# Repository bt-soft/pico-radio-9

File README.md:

# pico-radio-9

**A projekt még fejlesztés alatt áll!**

A projekt leírása: https://electrodiy.blog.hu/2026/01/01/pico_radio_fm_am_ssb_cw_rtty_sstv_wefax

## A kütyü

<br/>

<em>A kísérleti kütyü (egy V7-es prototípus hangfrekis műveleti erősítővel kiegészítve)</em>

<br/>

### PCB 3D View

<table style="border:none; width:100%;">
  <tr>
    <td style="border:none; text-align:center; vertical-align:middle;">
      
    </td>
    <td style="border:none; text-align:center; vertical-align:middle;">
      
    </td>
  </tr>
  <tr>
    <td style="border:none; text-align:center;">
      <em>Kétoldalas NYÁK terv</em>
    </td>
    <td style="border:none; text-align:center;">
      <em>Egyoldalas NYÁK terv</em>
    </td>
  </tr>
</table>

Egy Raspberry Pi Pico alapú rádióprojekt (Si4735 vezérléssel) — fejlett dekóderekkel (RTTY, CW, SSTV, WeFax), spektrum megjelenítéssel és interaktív érintőképernyős felülettel.

**Fő funkciók**
- Si4735 vezérlés (AM/FM/SDR jellegű demodok és RDS)
- Dekóderek: RTTY, CW, SSTV, WeFax, RTTY feldolgozó
- Valós idejű spektrum- és vízesés (low/high resolution bar, oscilloscope, envelope, waterfall, valamint CW/RTTY hangolássegéd waterfall és SNR burkoló) megjelenítők
- Hangfeldolgozó pipeline (AGC, FFT alapú vizualizáció manuális vagy automatikus erősítéssel)
- Rétegzett dialógus rendszer: többgombos dialógusok, értékmódosítók (rotary/touch)
- Konfigurációs tárolás EEPROM-ban (station/setting store)

## Architektúra
 - RP2040 / multicore: A Raspberry Pi Pico kétmagos RP2040 mikrovezérlője lehetővé teszi a feladatok elkülönítését (audio-feldolgozás a második magon, míg az első mag a UI/Si4735 vezérlést végzi). Ezt a projekt kihasználja a valós idejű audio dekódolás és UI műveletek párhuzamosítása érdekében.

## Technológiák

- Platform: Raspberry Pi Pico (RP2040)
- Fejlesztési környezet: PlatformIO 
- Framework: Arduino (RP2040 / Arduino core) 
- Nyelv: C++17 
- TFT vezérlés: `TFT_eSPI` — ILI9844 3.5" TFT grafikus megjelenítés és touch kezelése.
- Si4735 vezérlés: `PU2CLR SI4735` wrapper és a projekt saját `Si4735*` moduljai (I2C/SPI integráció és rádiófunkciók).
- Audio feldolgozás: FFT alapú spektrum- és vízesés (waterfall) megjelenítés, AGC és egyedi AudioProcessor pipeline.
- Dekóderek: RTTY, CW, SSTV, WeFax implementációk (saját `Decoder*` modulok).
- UI komponensek: egyedi komponenskeretrendszer (`UI*` osztályok) — dialógusok, többgombos menük, virtuális billentyűzet és grafikus komponensek.
- Időzítés és megszakítások: `RPI_PICO_TimerInterrupt` (PlatformIO lib) a pontos időzítéshez.
- FFT könyvtár: `arduinoFFT` a spektrum-számításokhoz.
- Helyi segédkönyvtárak: `lib/pico_sstv` az SSTV dekódoláshoz és segédfüggvényekhez.

## Felhasznált könyvtárak
- `Arduino-Pico`: https://github.com/earlephilhower/arduino-pico
- `TFT eSPI`: https://github.com/Bodmer/TFT_eSPI
- `RPI PICO TimerInterrupt`: https://github.com/khoih-prog/RPI_PICO_TimerInterrupt
- `PU2CLR SI4735`: https://github.com/pu2clr/SI4735
- `Arduino CMSIS-DSP`: https://www.arduinolibraries.info/libraries/arduino_cmsis-dsp
- `lib/pico_sstv`: https://github.com/dawsonjon/PicoSSTV

## Fájlok és modulok (összefoglaló)
- `src/` - forráskód (képernyők, dekóderek, UI komponensek, vezérlők)
  - `main.cpp`, `main-c1.cpp` - indító fájlok
  - `Screen*` - különböző képernyők (RTTY, CW, FM, AM, SSTV, WeFax, Setup, stb.)
  - `Decoder*` - dekóderek (RTTY, CW, SSTV, WeFax, stb.)
  - `UI*` - UI keretrensdszer komponensei (gombok, dialógusok, spektrum, textbox, stb.)
  - `Si4735*` - Si4735 kezelő és runtime logika
  - `AudioController.*`, `AudioProcessor-*` - audio pipeline és feldolgozás
- `include/` - header fájlok (összes osztály, UI, konfigurációs struktúrák)
  - `Config.h`, `ConfigData.h` - konfigurációs struktúrák és default értékek
  - `UIDialogBase.h`, `UIMultiButtonDialog.h`, `UIValueChangeDialog.h` - dialógusok és vezérlők
  - `UIHorizontalButtonBar.h` - alsó gombsor kezelése
- `lib/` - külső vagy saját könyvtárak (pl. `pico_sstv`, `CMSIS-DSP`)
- `doc/` - dokumentációs anyagok 
- `test/` - teszt erőforrások és példa adatállományok (pl. cw, rtty tesztek)

## Konfiguráció és mentés
- Konfigurációk a `Config` struktúrában találhatók (`include/Config.h`, `include/ConfigData.h`).
- Station / memory store beállítások EEPROM-ban tárolódnak (lásd `StationStore*` és `Eeprom*` fájlok).

## UI képernyők, dialógusok
- Rétegzett dialógus rendszer: a `UIScreen` tartalmaz egy dialógusstack-et, a `showDialog()` és `onDialogClosed()` mechanizmusokkal.
- Többgombos dialógusok: `UIMultiButtonDialog` + `UIValueChangeDialog` az értékek szerkesztéséhez.

## Szoftverarchitektúra
- Dekóderek: `src/Decoder*.cpp` — új dekóderek hozzáadása egyszerű az `IDecoder` interfész implementálásával.
- UI komponensek: `include/UI*`, `src/UI*` — gombok, dialógusok, új vizualizációk hozzáadása.
- Audio pipeline: `AudioController.cpp` és `AudioProcessor-*.cpp` fájlok tartalmazzák a feldolgozás logikáját.

## Hibakeresés / debug
- A forrásban `DEBUG(...)` makrók és logolási segédek találhatók. A debug build beállítása és a `__DEBUG` makró használata segíthet a problémakeresésben.

## Kapcsolási rajz / nyomtatott áramkör
- Kicad formátumban a `kicad` mappában (egy- és kétoldalas NYÁK tervvel).

---

## Harmadik féltől származó források
Az alábbi forrás nyújtottak inspirációkat a projekt fejlesztése és megvalósítása során.

 - **SI4735 + TFT példa (IU4ALH)**: https://github.com/IU4ALH/IU4ALH
  - Használat: Elsősorban a repó  `SI4735_2.8_TFT_SI5351_V.5.2b_Dark.zip` állományában található forrásokat használtam fel, amelyek inspirációt adtak a szolgáltatások, a képernyők felépítéséhez valamint az Si4735 beállítások kezeléséhez.

- **Rotary encoder / forgókapcsoló referencia**: https://www.mikrocontroller.net/articles/Drehgeber
  - Használat: A forgató encoder kezelésének elméleti háttere és debouncing/step logika inspirálására; segített a `RotaryEncoder` osztály és a forgóvezérlők finomhangolásában.

- **Pico SSTV implementáció**: https://github.com/dawsonjon/PicoSSTV
  - Használat: SSTV dekóder és mintafeldolgozó technikák inspirációjára használtam a projekt `DecoderSSTV` moduljának kialakításához.

- **fldigi**: https://github.com/w1hkj/fldigi
  - Használat: HF WeFax dekóder kiakalítása, technikai megoldások, szoftveres szűrők
---

## License
Projekt licenc: MIT

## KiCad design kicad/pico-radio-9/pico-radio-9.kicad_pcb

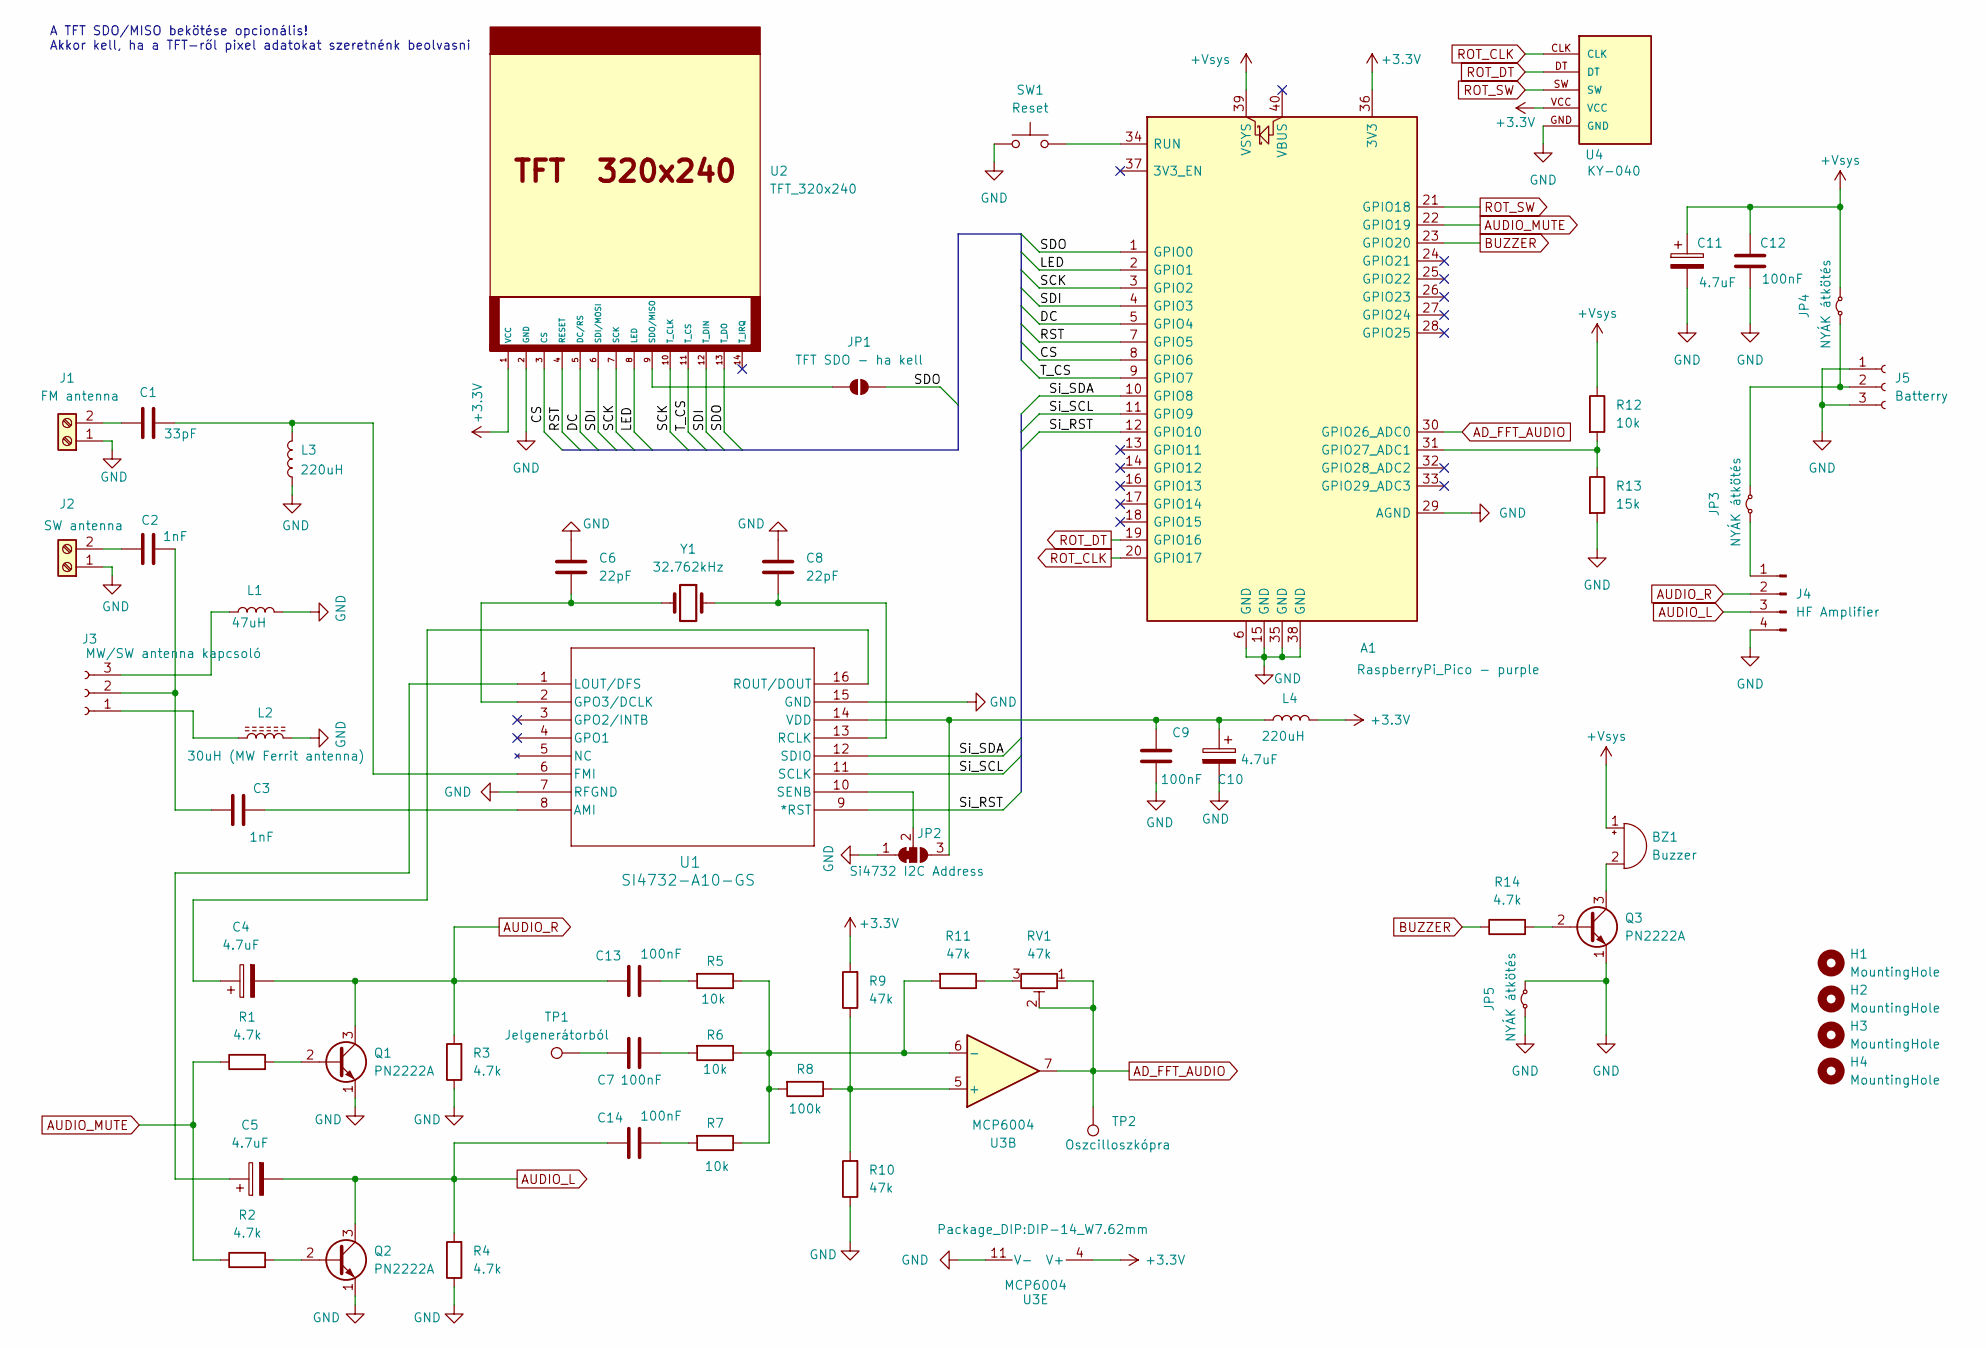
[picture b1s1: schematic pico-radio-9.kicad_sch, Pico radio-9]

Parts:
A1: RaspberryPi_Pico - purple; RaspberryPi_Pico_Common_THT-simple
BZ1: Buzzer; Buzzer_12x9.5RM7.6
C1: 33pF; C_Disc_D3.0mm_W1.6mm_P2.50mm
C2, C3: 1nF; C_Disc_D3.0mm_W1.6mm_P2.50mm
C4, C5, C10, C11: 4.7uF; CP_Radial_D5.0mm_P2.50mm
C6, C8: 22pF; C_Disc_D3.0mm_W1.6mm_P2.50mm
C7, C9, C12, C13, C14: 100nF; C_Disc_D7.0mm_W2.5mm_P5.00mm
H1, H2, H3, H4: MountingHole; MountingHole_3.2mm_M3
J1: FM antenna; TerminalBlock_4Ucon_1x02_P3.50mm_Horizontal
J2: SW antenna; TerminalBlock_4Ucon_1x02_P3.50mm_Horizontal
J3: MW/SW antenna kapcsoló; PinHeader_1x03_P2.54mm_Vertical
J4: HF Amplifier; PinHeader_1x04_P2.54mm_Vertical
J5: Batterry; PinHeader_1x03_P2.54mm_Vertical
JP1: TFT SDO - ha kell; SolderJumper-2_P1.3mm_Open_RoundedPad1.0x1.5mm
JP2: Si4732 I2C Address; SolderJumper-3_P1.3mm_Bridged12_RoundedPad1.0x1.5mm
JP3, JP4, JP5: NYÁK átkötés; R_Axial_DIN0207_L6.3mm_D2.5mm_P10.16mm_Horizontal
L1: 47uH; R_Axial_DIN0207_L6.3mm_D2.5mm_P10.16mm_Horizontal
L2: 30uH (MW Ferrit antenna); PinHeader_1x02_P2.54mm_Vertical
L3, L4: 220uH; R_Axial_DIN0207_L6.3mm_D2.5mm_P10.16mm_Horizontal
Q1, Q2, Q3: PN2222A; TO-92_Inline_Wide
R1, R2, R3, R4, R14: 4.7k; R_Axial_DIN0207_L6.3mm_D2.5mm_P10.16mm_Horizontal
R5, R6, R7, R12: 10k; R_Axial_DIN0207_L6.3mm_D2.5mm_P10.16mm_Horizontal
R8: 100k; R_Axial_DIN0207_L6.3mm_D2.5mm_P10.16mm_Horizontal
R9, R10, R11: 47k; R_Axial_DIN0207_L6.3mm_D2.5mm_P10.16mm_Horizontal
R13: 15k; R_Axial_DIN0207_L6.3mm_D2.5mm_P10.16mm_Horizontal
RV1: 47k; Potentiometer_Runtron_RM-063_Horizontal
SW1: Reset; PinHeader_1x02_P2.54mm_Vertical
TP1: Jelgenerátorból; TestPoint_Loop_D2.50mm_Drill1.0mm
TP2: Oszcilloszkópra; TestPoint_Loop_D2.50mm_Drill1.0mm
U1: SI4732-A10-GS; SOIC_A10-GS_SIL
U2: TFT_320x240; PinHeader_1x14_P2.54mm_Vertical
U3: MCP6004; DIP-14_W7.62mm
U4: KY-040; KY-040-PORT
Y1: 32.762kHz; Crystal_C38-LF_D3.0mm_L8.0mm_Horizontal

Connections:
+3.3V: A1.36 (3V3), L4.2, R9.2, U2.1 (VCC), U3.4 (V+), U4.VCC
+Vsys: A1.39 (VSYS), BZ1.1 (+), C11.1, C12.1, JP4.2 (B), R12.1
/CS: A1.8 (GPIO6), U2.3 (CS)
/DC: A1.5 (GPIO4), U2.5 (DC/RS)
/LED: A1.2 (GPIO1), U2.8 (LED)
/RST: A1.7 (GPIO5), U2.4 (RESET)
/SCK: A1.3 (GPIO2), U2.7 (SCK), U2.10 (T_CLK)
/SDI: A1.4 (GPIO3), U2.6 (SDI/MOSI), U2.12 (T_DIN)
/SDO: A1.1 (GPIO0), JP1.2 (B), U2.13 (T_DO)
/Si_RST: A1.12 (GPIO10), U1.9 (*RST)
/Si_SCL: A1.11 (GPIO9), U1.11 (SCLK)
/Si_SDA: A1.10 (GPIO8), U1.12 (SDIO)
/T_CS: A1.9 (GPIO7), U2.11 (T_CS)
AD_FFT_AUDIO: A1.30 (GPIO26_ADC0), RV1.1, RV1.2, TP2.1, U3.7
AUDIO_L: C5.2, C14.2, J4.3, Q2.3 (C), R4.2
AUDIO_MUTE: A1.22 (GPIO19), R1.1, R2.1
AUDIO_R: C4.2, C13.2, J4.2, Q1.3 (C), R3.2
BUZZER: A1.23 (GPIO20), R14.1
GND: A1.6 (GND), A1.15 (GND), A1.29 (AGND), A1.35 (GND), A1.38 (GND), C6.2, C8.1, C9.1, C10.2, C11.2, C12.2, J1.1, J2.1, J4.4, J5.1, J5.3, JP2.1 (A), JP5.1 (A), JP5.2 (B), L1.2, L2.2, L3.1, Q1.1 (E), Q2.1 (E), Q3.1 (E), R3.1, R4.1, R10.1, R13.2, SW1.1, U1.7 (RFGND), U1.15 (GND), U2.2 (GND), U3.11 (V-), U4.GND
unnamed: A1.31 (GPIO27_ADC1), R12.2, R13.1
unnamed: A1.34 (RUN), SW1.2
unnamed: BZ1.2 (-), Q3.3 (C)
unnamed: C7.1, R6.2
unnamed: C7.2, TP1.1
unnamed: C13.1, R5.2
unnamed: C14.1, R7.2
unnamed: C1.2, J1.2
unnamed: C2.1, J2.2
unnamed: J3.1, L2.1
unnamed: C2.2, C3.2, J3.2
unnamed: J3.3, L1.1
unnamed: J4.1, JP3.1 (A)
unnamed: J5.2, JP3.2 (B), JP4.1 (A)
unnamed: JP1.1 (A), U2.9 (SDO/MISO)
unnamed: C9.2, C10.1, JP2.3 (B), L4.1, U1.14 (VDD)
unnamed: JP2.2 (C), U1.10 (SENB)
unnamed: Q1.2 (B), R1.2
unnamed: Q2.2 (B), R2.2
unnamed: Q3.2 (B), R14.2
unnamed: R11.1, RV1.3
unnamed: C3.1, U1.8 (AMI)
unnamed: C1.1, L3.2, U1.6 (FMI)
unnamed: C6.1, U1.2 (GPO3/DCLK), Y1.2
unnamed: C5.1, U1.1 (LOUT/DFS)
unnamed: C8.2, U1.13 (RCLK), Y1.1
unnamed: C4.1, U1.16 (ROUT/DOUT)
unnamed: R8.1, R9.1, R10.2, U3.5 (+)
unnamed: R5.1, R6.1, R7.1, R8.2, R11.2, U3.6 (-)
ROT_CLK: A1.20 (GPIO17), U4.CLK
ROT_DT: A1.19 (GPIO16), U4.DT
ROT_SW: A1.21 (GPIO18), U4.SW

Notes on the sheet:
A TFT SDO/MISO bekötése opcionális! Akkor kell, ha a TFT-ről pixel adatokat szeretnénk beolvasni

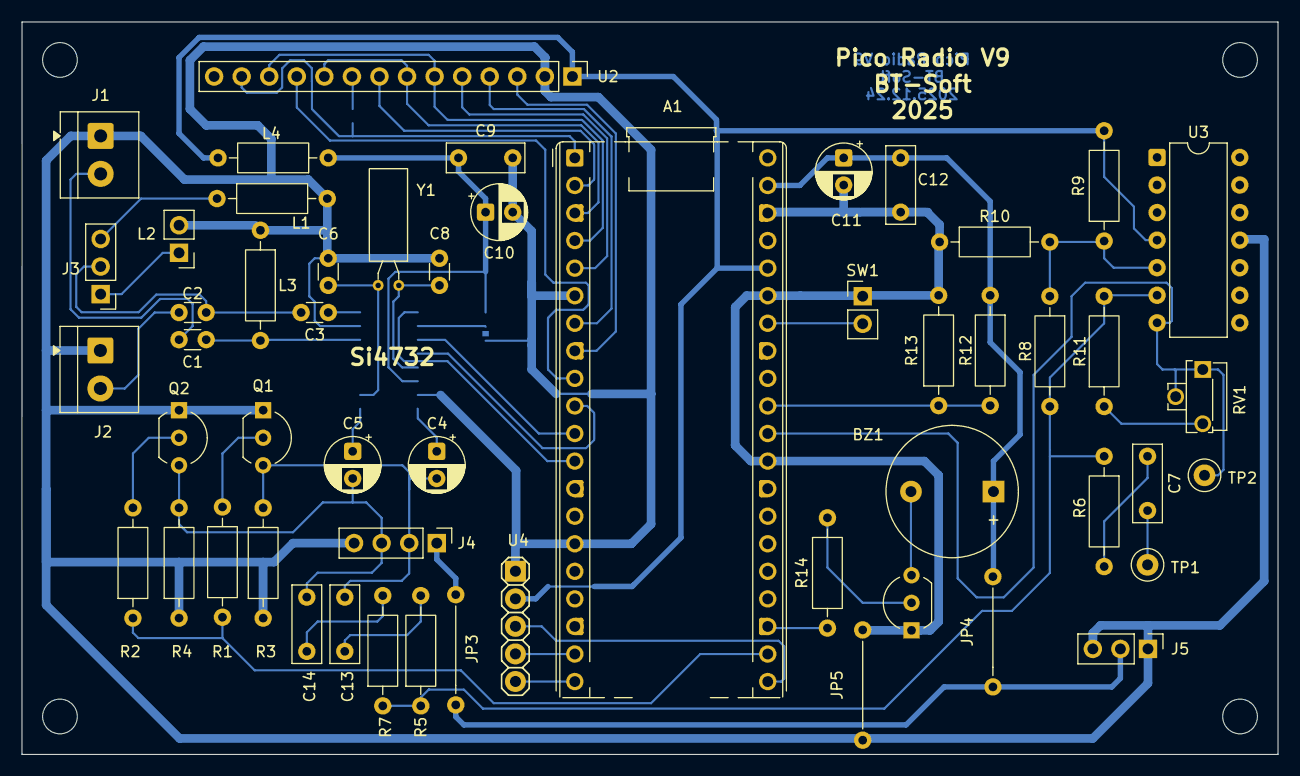
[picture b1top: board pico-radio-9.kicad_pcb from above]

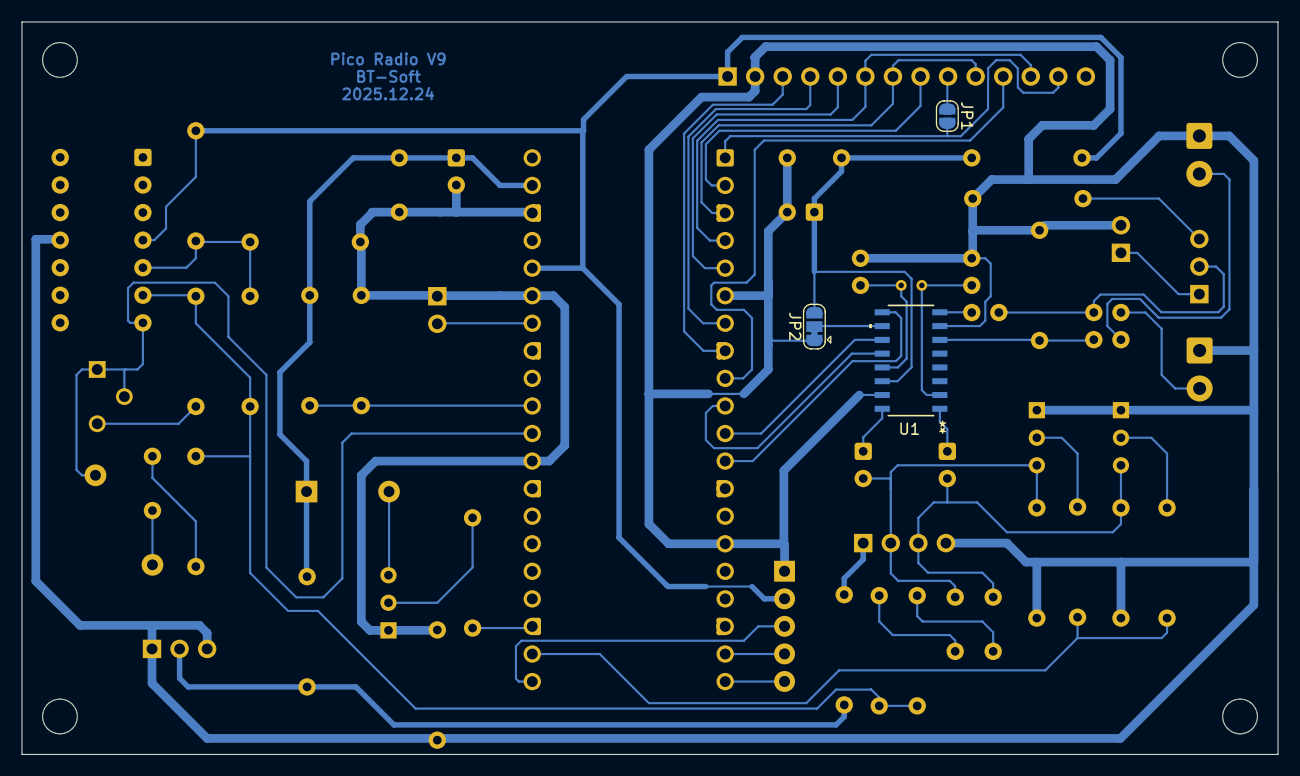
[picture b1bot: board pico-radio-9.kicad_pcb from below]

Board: 2 copper layers, 115.8 x 67.5 mm, 60 parts (3 on the bottom side), 51 nets.

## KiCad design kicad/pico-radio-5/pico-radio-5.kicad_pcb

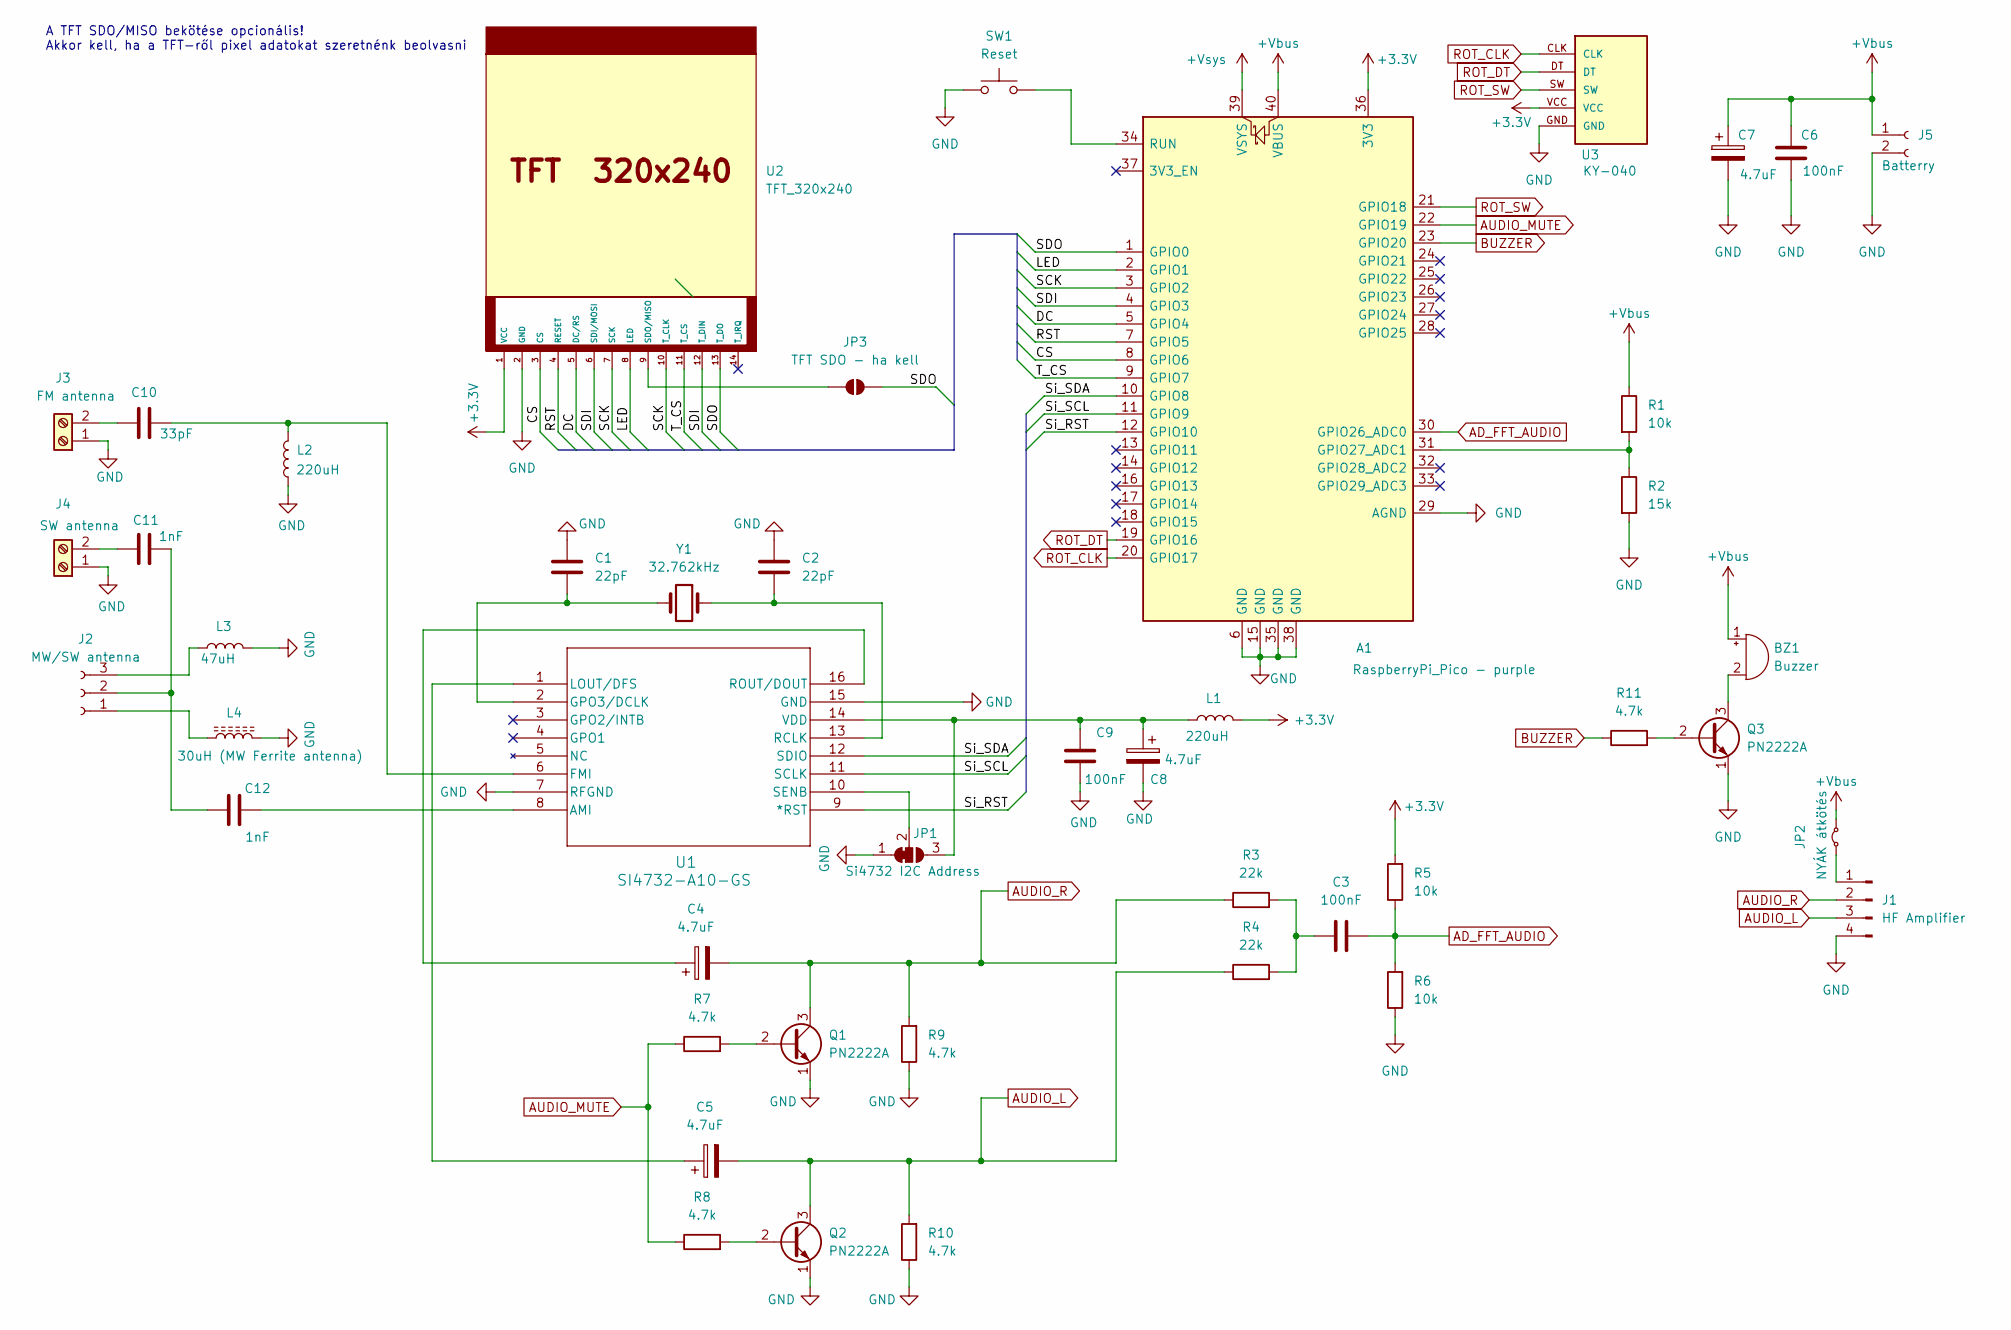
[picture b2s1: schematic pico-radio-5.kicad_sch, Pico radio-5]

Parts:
A1: RaspberryPi_Pico - purple; RaspberryPi_Pico_Common_THT-simple
BZ1: Buzzer; Buzzer_12x9.5RM7.6
C1, C2: 22pF; C_Disc_D3.0mm_W1.6mm_P2.50mm
C3, C6, C9: 100nF; C_Disc_D7.0mm_W2.5mm_P5.00mm
C4, C5, C7, C8: 4.7uF; CP_Radial_D5.0mm_P2.50mm
C10: 33pF; C_Disc_D3.0mm_W1.6mm_P2.50mm
C11, C12: 1nF; C_Disc_D3.0mm_W1.6mm_P2.50mm
J1: HF Amplifier; PinHeader_1x04_P2.54mm_Vertical
J2: MW/SW antenna; PinHeader_1x03_P2.54mm_Vertical
J3: FM antenna; TerminalBlock_4Ucon_1x02_P3.50mm_Horizontal
J4: SW antenna; TerminalBlock_4Ucon_1x02_P3.50mm_Horizontal
J5: Batterry; PinHeader_1x02_P2.54mm_Vertical
JP1: Si4732 I2C Address; SolderJumper-3_P1.3mm_Bridged12_RoundedPad1.0x1.5mm
JP2: NYÁK átkötés; R_Axial_DIN0207_L6.3mm_D2.5mm_P10.16mm_Horizontal
JP3: TFT SDO - ha kell; SolderJumper-2_P1.3mm_Open_RoundedPad1.0x1.5mm
L1, L2: 220uH; R_Axial_DIN0207_L6.3mm_D2.5mm_P10.16mm_Horizontal
L3: 47uH; R_Axial_DIN0207_L6.3mm_D2.5mm_P10.16mm_Horizontal
L4: 30uH (MW Ferrite antenna); PinHeader_1x02_P2.54mm_Vertical
Q1, Q2, Q3: PN2222A; TO-92_Inline
R1, R5, R6: 10k; R_Axial_DIN0207_L6.3mm_D2.5mm_P10.16mm_Horizontal
R2: 15k; R_Axial_DIN0207_L6.3mm_D2.5mm_P10.16mm_Horizontal
R3, R4: 22k; R_Axial_DIN0207_L6.3mm_D2.5mm_P10.16mm_Horizontal
R7, R8, R9, R10, R11: 4.7k; R_Axial_DIN0207_L6.3mm_D2.5mm_P10.16mm_Horizontal
SW1: Reset; PinHeader_1x02_P2.54mm_Vertical
U1: SI4732-A10-GS; SOIC_A10-GS_SIL
U2: TFT_320x240; PinHeader_1x14_P2.54mm_Vertical
U3: KY-040; KY-040-PORT
Y1: 32.762kHz; Crystal_C38-LF_D3.0mm_L8.0mm_Horizontal

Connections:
+3.3V: A1.36 (3V3), L1.2, R5.2, U2.1 (VCC), U3.VCC
+Vbus: A1.40 (VBUS), BZ1.1 (+), C6.1, C7.1, J5.1, JP2.2 (B), R1.1
+Vsys: A1.39 (VSYS)
/CS: A1.8 (GPIO6), U2.3 (CS)
/DC: A1.5 (GPIO4), U2.5 (DC/RS)
/LED: A1.2 (GPIO1), U2.8 (LED)
/RST: A1.7 (GPIO5), U2.4 (RESET)
/SCK: A1.3 (GPIO2), U2.7 (SCK), U2.10 (T_CLK)
/SDI: A1.4 (GPIO3), U2.6 (SDI/MOSI), U2.12 (T_DIN)
/SDO: A1.1 (GPIO0), JP3.2 (B), U2.13 (T_DO)
/Si_RST: A1.12 (GPIO10), U1.9 (*RST)
/Si_SCL: A1.11 (GPIO9), U1.11 (SCLK)
/Si_SDA: A1.10 (GPIO8), U1.12 (SDIO)
/T_CS: A1.9 (GPIO7), U2.11 (T_CS)
AD_FFT_AUDIO: A1.30 (GPIO26_ADC0), C3.2, R5.1, R6.2
AUDIO_L: C5.2, J1.3, Q2.3 (C), R4.1, R10.2
AUDIO_MUTE: A1.22 (GPIO19), R7.1, R8.1
AUDIO_R: C4.2, J1.2, Q1.3 (C), R3.1, R9.2
BUZZER: A1.23 (GPIO20), R11.1
GND: A1.6 (GND), A1.15 (GND), A1.29 (AGND), A1.35 (GND), A1.38 (GND), C1.2, C2.1, C6.2, C7.2, C8.2, C9.1, J1.4, J3.1, J4.1, J5.2, JP1.1 (A), L2.1, L3.2, L4.2, Q1.1 (E), Q2.1 (E), Q3.1 (E), R2.2, R6.1, R9.1, R10.1, SW1.1, U1.7 (RFGND), U1.15 (GND), U2.2 (GND), U3.GND
unnamed: A1.31 (GPIO27_ADC1), R1.2, R2.1
unnamed: A1.34 (RUN), SW1.2
unnamed: BZ1.2 (-), Q3.3 (C)
unnamed: C3.1, R3.2, R4.2
unnamed: J1.1, JP2.1 (A)
unnamed: J2.1, L4.1
unnamed: C11.2, C12.2, J2.2
unnamed: J2.3, L3.1
unnamed: C10.2, J3.2
unnamed: C11.1, J4.2
unnamed: C8.1, C9.2, JP1.3 (B), L1.1, U1.14 (VDD)
unnamed: JP1.2 (C), U1.10 (SENB)
unnamed: JP3.1 (A), U2.9 (SDO/MISO)
unnamed: Q1.2 (B), R7.2
unnamed: Q2.2 (B), R8.2
unnamed: Q3.2 (B), R11.2
unnamed: C12.1, U1.8 (AMI)
unnamed: C10.1, L2.2, U1.6 (FMI)
unnamed: C1.1, U1.2 (GPO3/DCLK), Y1.2
unnamed: C5.1, U1.1 (LOUT/DFS)
unnamed: C2.2, U1.13 (RCLK), Y1.1
unnamed: C4.1, U1.16 (ROUT/DOUT)
ROT_CLK: A1.20 (GPIO17), U3.CLK
ROT_DT: A1.19 (GPIO16), U3.DT
ROT_SW: A1.21 (GPIO18), U3.SW

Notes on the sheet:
A TFT SDO/MISO bekötése opcionális! Akkor kell, ha a TFT-ről pixel adatokat szeretnénk beolvasni

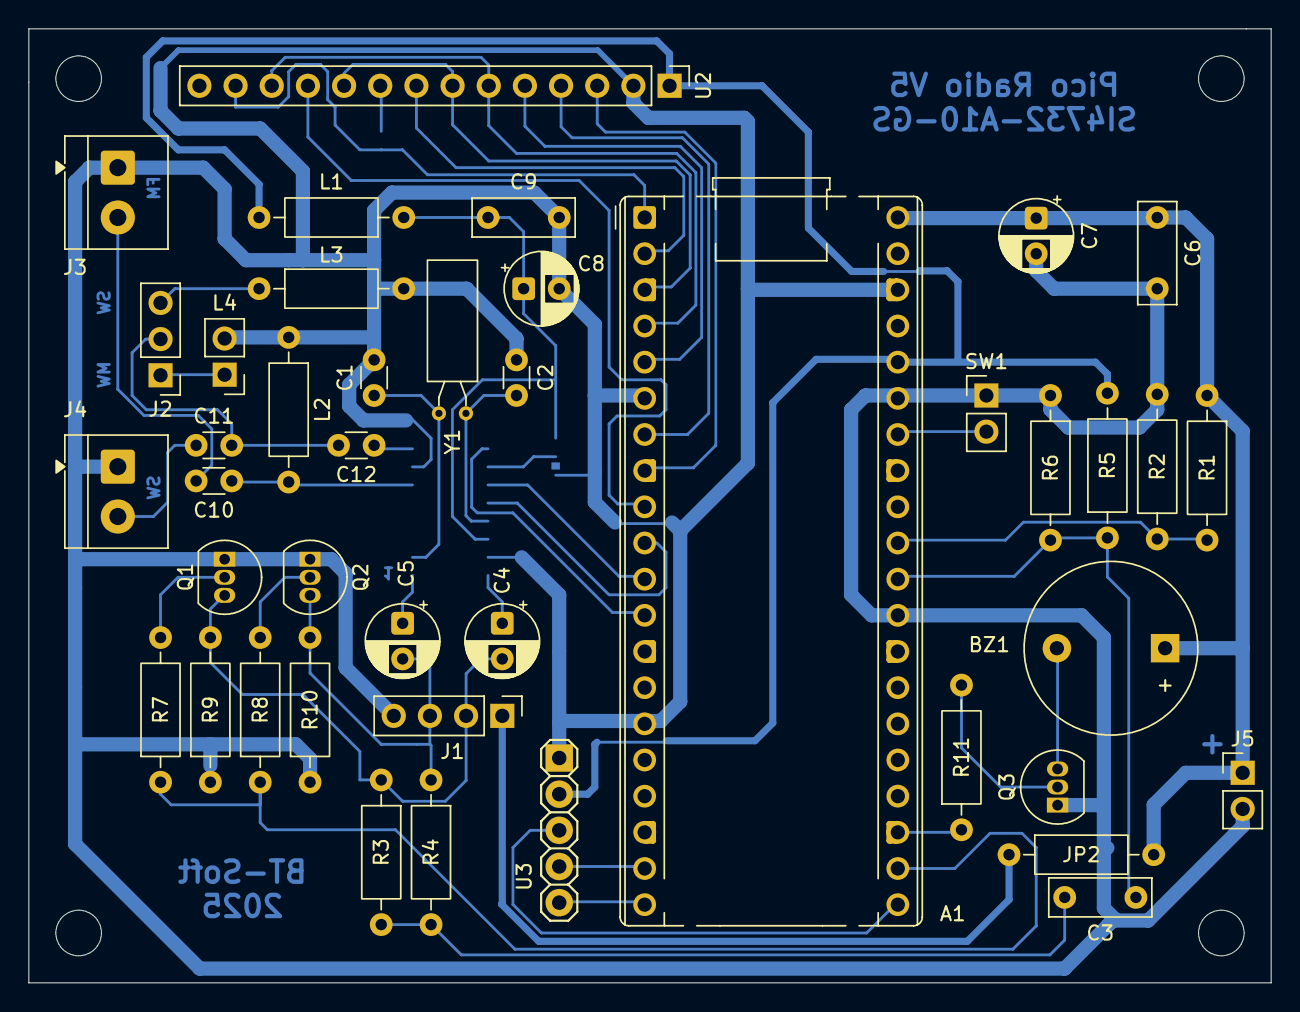
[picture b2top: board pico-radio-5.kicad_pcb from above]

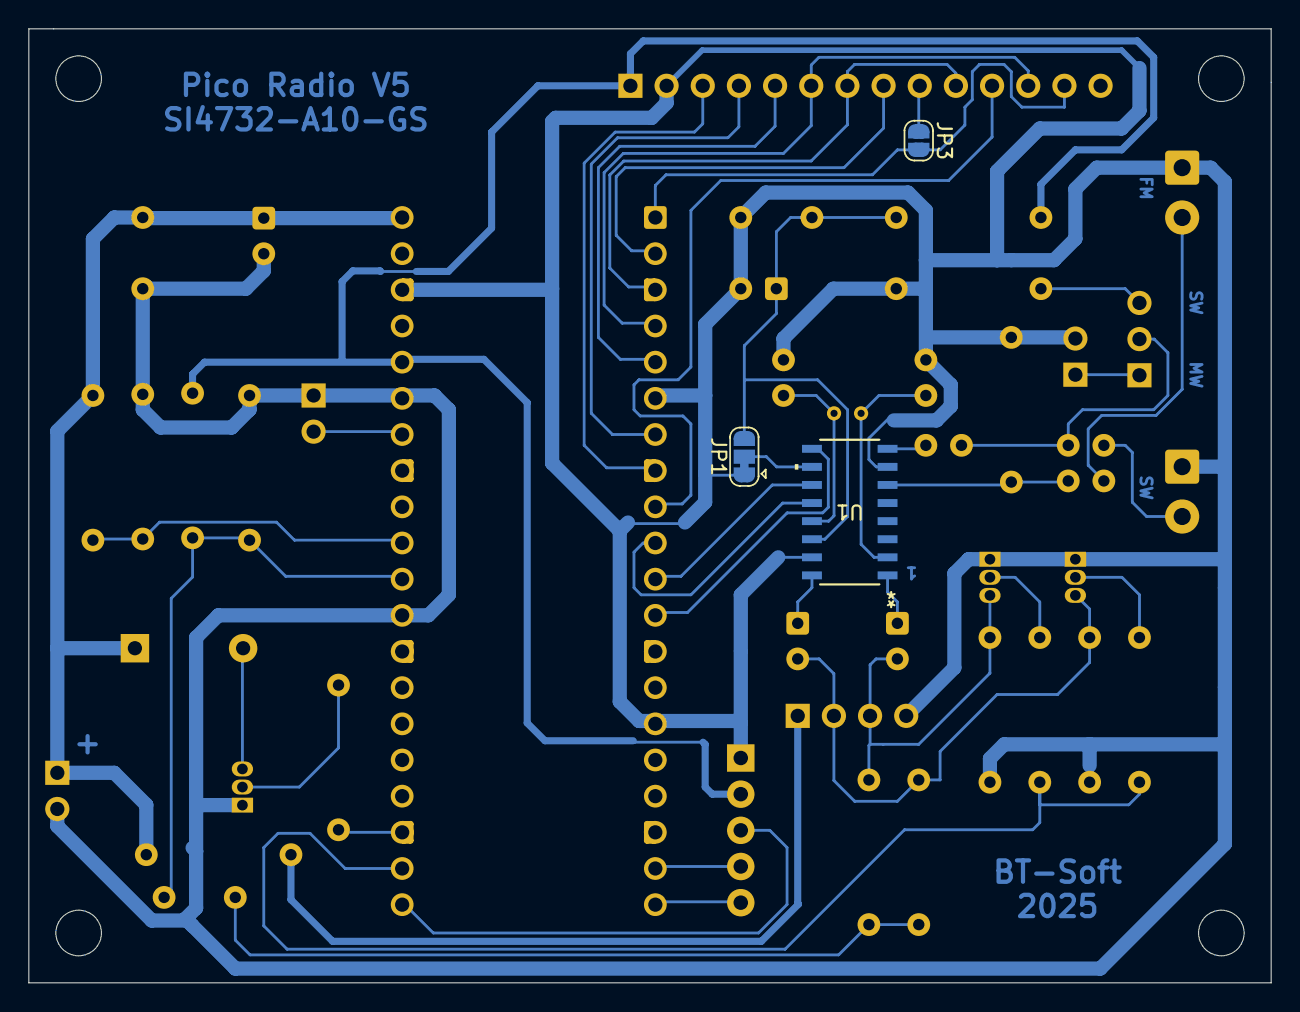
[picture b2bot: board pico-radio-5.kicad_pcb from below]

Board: 2 copper layers, 87.2 x 67.0 mm, 45 parts (3 on the bottom side), 44 nets.

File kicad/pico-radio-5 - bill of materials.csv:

"Id";"Designator";"Footprint";"Quantity";"Designation";"Supplier and ref";
1;"Q3,Q1,Q2";"TO-92_Inline";3;"PN2222A";;;
2;"L1,L3";"R_Axial_DIN0207_L6.3mm_D2.5mm_P10.16mm_Horizontal";2;"47uH";;;
3;"C9,C6,C3";"C_Disc_D7.0mm_W2.5mm_P5.00mm";3;"100nF";;;
4;"C8,C7,C5,C4";"CP_Radial_D5.0mm_P2.50mm";4;"4.7uF";;;
5;"SW1";"PinHeader_1x02_P2.54mm_Vertical";1;"Reset";;;
6;"J2";"PinHeader_1x03_P2.54mm_Vertical";1;"MW/SW antenna";;;
7;"R3,R4";"R_Axial_DIN0207_L6.3mm_D2.5mm_P10.16mm_Horizontal";2;"22k";;;
8;"L2";"R_Axial_DIN0207_L6.3mm_D2.5mm_P10.16mm_Horizontal";1;"270uH";;;
9;"JP2";"R_Axial_DIN0207_L6.3mm_D2.5mm_P10.16mm_Horizontal";1;"NYÁK átkötés";;;
10;"R7,R10,R11,R9,R8";"R_Axial_DIN0207_L6.3mm_D2.5mm_P10.16mm_Horizontal";5;"4.7k";;;
11;"C2,C1";"C_Disc_D3.0mm_W1.6mm_P2.50mm";2;"22pF";;;
12;"U2";"PinHeader_1x14_P2.54mm_Vertical";1;"TFT_320x240";;;
13;"J3";"TerminalBlock_4Ucon_1x02_P3.50mm_Horizontal";1;"FM antenna";;;
14;"J1";"PinHeader_1x04_P2.54mm_Vertical";1;"HF Amplifier";;;
15;"Y1";"Crystal_C38-LF_D3.0mm_L8.0mm_Horizontal";1;"32.762kHz";;;
16;"J5";"PinHeader_1x02_P2.54mm_Vertical";1;"Batterry";;;
17;"C12,C11";"C_Disc_D3.0mm_W1.6mm_P2.50mm";2;"1nF";;;
18;"L4";"PinHeader_1x02_P2.54mm_Vertical";1;"30uH (MW Ferrite antenna)";;;
19;"R5,R6";"R_Axial_DIN0207_L6.3mm_D2.5mm_P10.16mm_Horizontal";2;"10k";;;
20;"J4";"TerminalBlock_4Ucon_1x02_P3.50mm_Horizontal";1;"SW antenna";;;
21;"U3";"KY-040-PORT";1;"KY-040";;;
22;"R1";"R_Axial_DIN0207_L6.3mm_D2.5mm_P10.16mm_Horizontal";1;"200k";;;
23;"A1";"RaspberryPi_Pico_Common_THT-simple";1;"RaspberryPi_Pico - purple";;;
24;"BZ1";"Buzzer_12x9.5RM7.6";1;"Buzzer";;;
25;"C10";"C_Disc_D3.0mm_W1.6mm_P2.50mm";1;"33pF";;;
26;"R2";"R_Axial_DIN0207_L6.3mm_D2.5mm_P10.16mm_Horizontal";1;"100k";;;
27;"U1";"SOIC_A10-GS_SIL";1;"SI4732-A10-GS";;;

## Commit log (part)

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2025-11-07 Audio test files
2025-11-07 Refactor command and response codes to use RP2040-specific enums for clarity
2025-11-07 Update program version to v9 and add SplashScreen class for initialization display
2025-11-08 UI framework base
2025-11-08 Add ScreenSaver and VirtualKeyboardDialog implementations
    - Implemented ScreenScreenSaver class for managing screen saver functionality, including animation and frequency display.
    - Added methods for activating and deactivating the screen saver, handling touch and rotary events, and updating frequency and battery display.
    - Created UIVirtualKeyboardDialog class for a virtual keyboard interface, including key handling, cursor management, and dynamic button states.
    - Enhanced user interaction with features like shift key functionality and special key handling (backspace, clear).
    - Improved visual feedback with cursor blinking and input field updates.
2025-11-08 UICompSpectrumVis
2025-11-08 Rename AudioController methods for clarity and update debug logging; adjust FM audio bandwidth settings
2025-11-09 Adjust FM audio raw samples size from 1024 to 512 for optimized processing
2025-11-09 Enhance UICompSpectrumVis to track dialog state and update frequency label rendering for improved clarity
2025-11-09 Add ScreenAMCW implementation for CW decoder functionality and UI integration
2025-11-09 Enhance FFT parameter handling for CW and RTTY display modes in UICompSpectrumVis
2025-11-10 Refactor dialog handling in UI components and remove unused drawContent method in ScreenAMCW
2025-11-10 Adjust label positioning above the textbox in checkDecodedData for improved alignment
2025-11-10 Fix CLEAR_AREA_WIDTH constant to correct display area size
2025-11-11 Refactor RDS component and update debug settings; remove unused debug defines and improve update logic
2025-11-11 Refactor UICompTextBox and Utils for type consistency; change parameter types to uint16_t and remove unused displayException function
2025-11-12 Refactor and cleanup codebase
    - Updated debug message handling in defines.h to clarify serial wait functionality.
    - Removed obsolete bill of materials CSV file from KiCad project.
    - Deleted outdated backup ZIP files from KiCad project.
    - Added USB serial port settings in platformio.ini for improved monitoring.
    - Enhanced AudioProcessorC1 class to manage DMA sampling state more effectively.
    - Cleaned up debug messages in ScreenAM and ScreenAMCW classes for better readability.
2025-11-13 Add RTTY functionality and refactor related components
    - Introduced ScreenAMRTTY for RTTY decoding display and handling.
    - Updated configuration structure to include rttyShiftFrequency and rttyBaudRate.
    - Refactored existing code to replace rttyShiftHz with rttyShiftFrequency.
    - Enhanced UI components to support RTTY settings and display.
    - Updated debug output to reflect new RTTY parameters.
2025-11-14 HWSW mutestat + kicad file rename
2025-11-14 Refactor audio gain settings and noise threshold; update scaling logic and debug output for FFT processing
2025-11-14 Refactor spectrum visualization methods and update color palette; rename functions for clarity and adjust noise threshold
2025-11-14 Add AGC buffer for maximum bar values and improve height adjustment logic
2025-11-14 Update gain update interval and improve debug logging in spectrum visualization
2025-11-14 Refactor debug logging in UICompSpectrumVis to use UISPECTRUM_DEBUG macro for consistency
2025-11-15 Update AGC target height utilization and adjust audio FFT gain settings for improved performance; refine sensitivity factors for CW and RTTY tuning aids
2025-11-15 Add SSTV and WeFax decoder screens; refactor existing screen definitions
2025-11-15 Update SSTV picture start position and clean up layoutComponents method
2025-11-15 Refactor horizontal button state management and streamline activation process across AM radio screens
2025-11-15 Refactor SNR and Tuning Aid sensitivity factors for CW/RTTY modes; streamline AGC application logic
2025-11-16 Update last modified timestamps and enhance memory status updates in ScreenAM and ScreenFM activation methods
2025-11-16 Implement RTTY parameter dialogs for frequency and baud rate adjustments; refactor related methods in ScreenAMRTTY and ScreenSetupAudioProc
2025-11-16 Update last modified timestamp and refactor RTTY display update logic in ScreenAMRTTY
2025-11-16 Remove outdated documentation and example code for AGC and noise reduction features
    - Deleted AGC and noise reduction usage guide (AGC_es_Zajszures_Hasznalat.md)
    - Removed example code demonstrating AGC and noise reduction usage (AudioProcessor_AGC_Pelda.cpp)
    - Eliminated technical explanation of noise reduction effects on FFT and decoders (Zajszures_FFT_Hatas_Technikai.md)
    - Removed command and response code definitions for RP2040 FIFO communication (RP2040CommandCode.h, RP2040ResponseCode.h)
2025-11-16 Refactor README.md: Update UI section header and improve dialog descriptions for clarity
2025-11-16 Update main-c1.cpp: Modify last modified timestamp and change static functions to public
2025-11-17 Update decoder_api.h, Si4735Rds.cpp, and UICompRDS.cpp: Modify last modified timestamps and enable debug definitions
2025-11-22 Update multiple files: Modify last modified timestamps, refactor checkSignalThreshold function, and enhance frequency tracking logic
2025-11-22 Update DecoderCW_C1 and ScreenAMCW: Modify last modified timestamps, adjust minimum threshold value, and enable adaptive AGC threshold in ScreenAMCW.
2025-11-22 Update UICompSpectrumVis and AudioProcessor: Modify last modified timestamps, adjust AGC history size type, and enhance FFT Gaussian window function documentation.
2025-11-22 Update AudioProcessor-c1 and ScreenSetupAudioProc: Modify last modified timestamps, enable ADPROC_DEBUG, and implement gain adjustment for FFT magnitude values.
2025-11-22 Update DecoderSSTV-c1: Modify last modified timestamp, enable SSTV_DEBUG, and format code for clarity
2025-11-22 Update decoders and screens: add reset functionality, modify last modified timestamps, and fix method names
2025-11-22 Update last modified timestamps and enhance RTTY settings display in ScreenAMRTTY
2025-11-25 Update last modified timestamps and enhance frequency tracking logic in DecoderCW_C1
2025-11-28 Refactor magnitude data handling to use static_cast for Q15 to float conversion in UICompSpectrumVis
2025-11-29 Refactor Q15 to float conversions and optimize rendering in UICompSpectrumVis
2025-11-29 Update FFT usage methods and modify timestamps in audio processing files
2025-11-29 Update last modified timestamps and correct audio frequency constant naming
2025-11-29 Update last modified timestamp and refine FFT output rescaling logic
2025-11-29 Refactor scaling factors from Q8 to Q16 for improved precision in spectrum visualization
2025-11-29 Add ADC DC midpoint calibration and initialization for audio processing
    - Introduced `init()` method in `AudioController` to request ADC DC midpoint calibration from Core1.
    - Added `calibrateDcMidpoint()` method in `AudioProcessorC1` for runtime measurement of ADC midpoint.
    - Updated command handling in `main-c1.cpp` to process DC calibration command.
    - Adjusted audio controller setup to include ADC calibration during initialization.
2025-11-30 Update last modified timestamps and refactor bandwidth scale calculations for improved clarity and maintainability
2025-11-30 Refactor gain calculations to use dB instead of percentage for improved accuracy and performance
2025-11-30 Enhance oscilloscope rendering with center line and soft-knee gain adjustments for improved visualization
2025-11-30 Refactor clamping logic to use constrain function for improved readability and maintainability across multiple files
2025-11-30 Refactor debug logging in UICompSpectrumVis for improved clarity and localization
2025-12-01 Refactor gain calculations to use 32-bit native operations for improved performance and clarity; update related functions for consistency and backward compatibility with float gain versions.
2025-12-01 Update bandwidth gain table for CW and AM modes; adjust gain values for improved audio performance and consistency
2025-12-01 Refactor tuning aid rendering to use consistent padding; update comments for clarity in CW and RTTY modes
2025-12-02 Refactor bandwidth gain table for clarity; update mode availability checks and optimize SNR curve rendering logic
2025-12-02 Enhance RTTY decoder documentation and parameters; update noise handling constants for improved performance
2025-12-03 Enhance RTTY decoder with fldigi-based envelope tracking and adaptive threshold; implement decay average for signal processing and update AGC parameters for improved performance
2025-12-14 Refactor button configuration in ScreenAM and ScreenAMRadioBase for improved readability; update last modified timestamps
2025-12-18 Update last modified timestamps and enhance debug logging frequency in AudioProcessor and main files
2025-12-19 Update last modified timestamp and comment out RDS debug definition in UICompRDS
2025-12-20 Update last modified timestamp format and remove debug output from FFT processing
2025-12-20 Refactor spectrum visualization: implement logarithmic scaling for pixel height conversion to enhance dynamic range
2025-12-21 Refactor spectrum bar rendering: change FFT magnitude reference point to const, implement low-res gain boost, and clarify reference magnitude calculations
2025-12-21 Refactor debug logging: update timestamps in multiple files, enable debug flags for RDS and spectrum visualization, and adjust gain settings for improved performance
2025-12-21 Refactor audio processing and spectrum visualization: implement fixed input scaling for consistent UI display, enhance baseline gain constants for various modes, and adjust gain calculation limits fo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
2025-12-21 Refactor WeFax decoder: update debug messages for clarity, adjust phasing detection thresholds, and streamline transition conditions for improved performance.
2025-12-22 Refactor spectrum visualization: implement drawBarArea helper function for improved rendering of spectrum bars and peaks in high-resolution mode.
2025-12-22 Update debug logging and metadata in audio processing modules
    - Updated last modified dates in AudioProcessor-c1.cpp, DecoderCW-c1.cpp, and DecoderWeFax-c1.cpp.
    - Commented out debug logging statements in AudioProcessor-c1.cpp to reduce verbosity.
    - Added conditional compilation for debug logging in DecoderCW-c1.cpp to enable/disable debug output based on __CW_DEBUG flag.
    - Commented out the calculation of signal_white_ratio in DecoderWeFax-c1.cpp to prevent unnecessary computation.
2025-12-22 Update UIColorPalette and ScreenScreenSaver: modify battery color definitions and improve code formatting
2025-12-22 Update RTTY parameter dialogs: rename Space frequency dialog to Shift frequency, add preset buttons, and adjust layout
2025-12-24 -Print DC offset voltage in the log during init - Double-sided PCB design start
2025-12-25 PCB fabric order files
2025-12-26 Refactor comments and debug messages for clarity and consistency in DecoderWeFax-C1
2025-12-26 Enhance UICompTuningBar to include configurable gain parameter and update related components; remove obsolete test audio files.
2025-12-26 Update PCB 3D View section in README.md to enhance layout and presentation of images
2025-12-29 Remove outdated backup ZIP files from the repository
2026-01-05 Dual sided PCB
2026-01-05 Fix display mode text formatting and add gain constraint for oscilloscope rendering
2026-01-07 Refactor spectrum visualization constants and functions for clarity and maintainability
    - Organized constants related to visualization, AGC, and color palettes into clearly defined sections.
    - Updated baseline gain constants and added detailed documentation for clarity.
    - Improved the calculation of AGC gain with a focus on RMS-based methods and added smoothing factors.
    - Enhanced normalization functions for dBFS values to ensure consistent scaling across visualizations.
    - Deprecated old linear conversion functions in favor of new dBFS-based methods for better accuracy and reliability.
    - Added detailed comments and documentation throughout the code for better understanding and maintainabilit
